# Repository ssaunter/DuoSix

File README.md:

# DuoSix
DuoSix is a 6-key, dual-encoder macropad powered by a Seeed Studio XIAO RP2040 and a PCF8574N IO Expander. 

Right now, the buttons are just bound to media controls, but I intend to update the code in the future to store "libraries" of key presets based on different apps or uses, which can be navigated and selected through the OLED and one of the encoders.

I made this project to learn how to use some new programs, while challenging myself to make something that I'll want to use for a long time. While I have experience in CAD and some of EDA in fusion, I had zero expereience in KiCad or Github before this project, so figuring everything out over about four days felt great.

---
**DuoSix Full Assembly**

---

**KiCad Schematic**

---

**KiCad PCB Routing**

---

**Case and PCB Fitment**

This design utilizes mostly press-fit connection. The PCB is mounted to the bottom case using M3x6 screws, and the diffusing ring is set in place around it, and in contact with the base. The diffusing ring is then slotted into the top case, holding the case together. I also made knobs to press-fit onto the rotary encoders.

---
### Bill of Materials (BOM)

**Included:**
* 1x Seeed Studio XIAO RP2040
* 6x MX-Style switches
* 6x DSA keycaps
* 2x EC11 rotary encoders
* 1x 0.91 inch OLED display
* 6x 1N4148 diodes
* 8x SK6812 MINI-E LEDs
* 4x M3x5mx4mm heatset inserts
* 3D Printed Case Components (Top, Bottom, Diffuser)

**Self Sourced:**
* 1x PCF8574N IO expander
* 1x 4 pin female socket (raises OLED up)
* 4x M3x6mm screws

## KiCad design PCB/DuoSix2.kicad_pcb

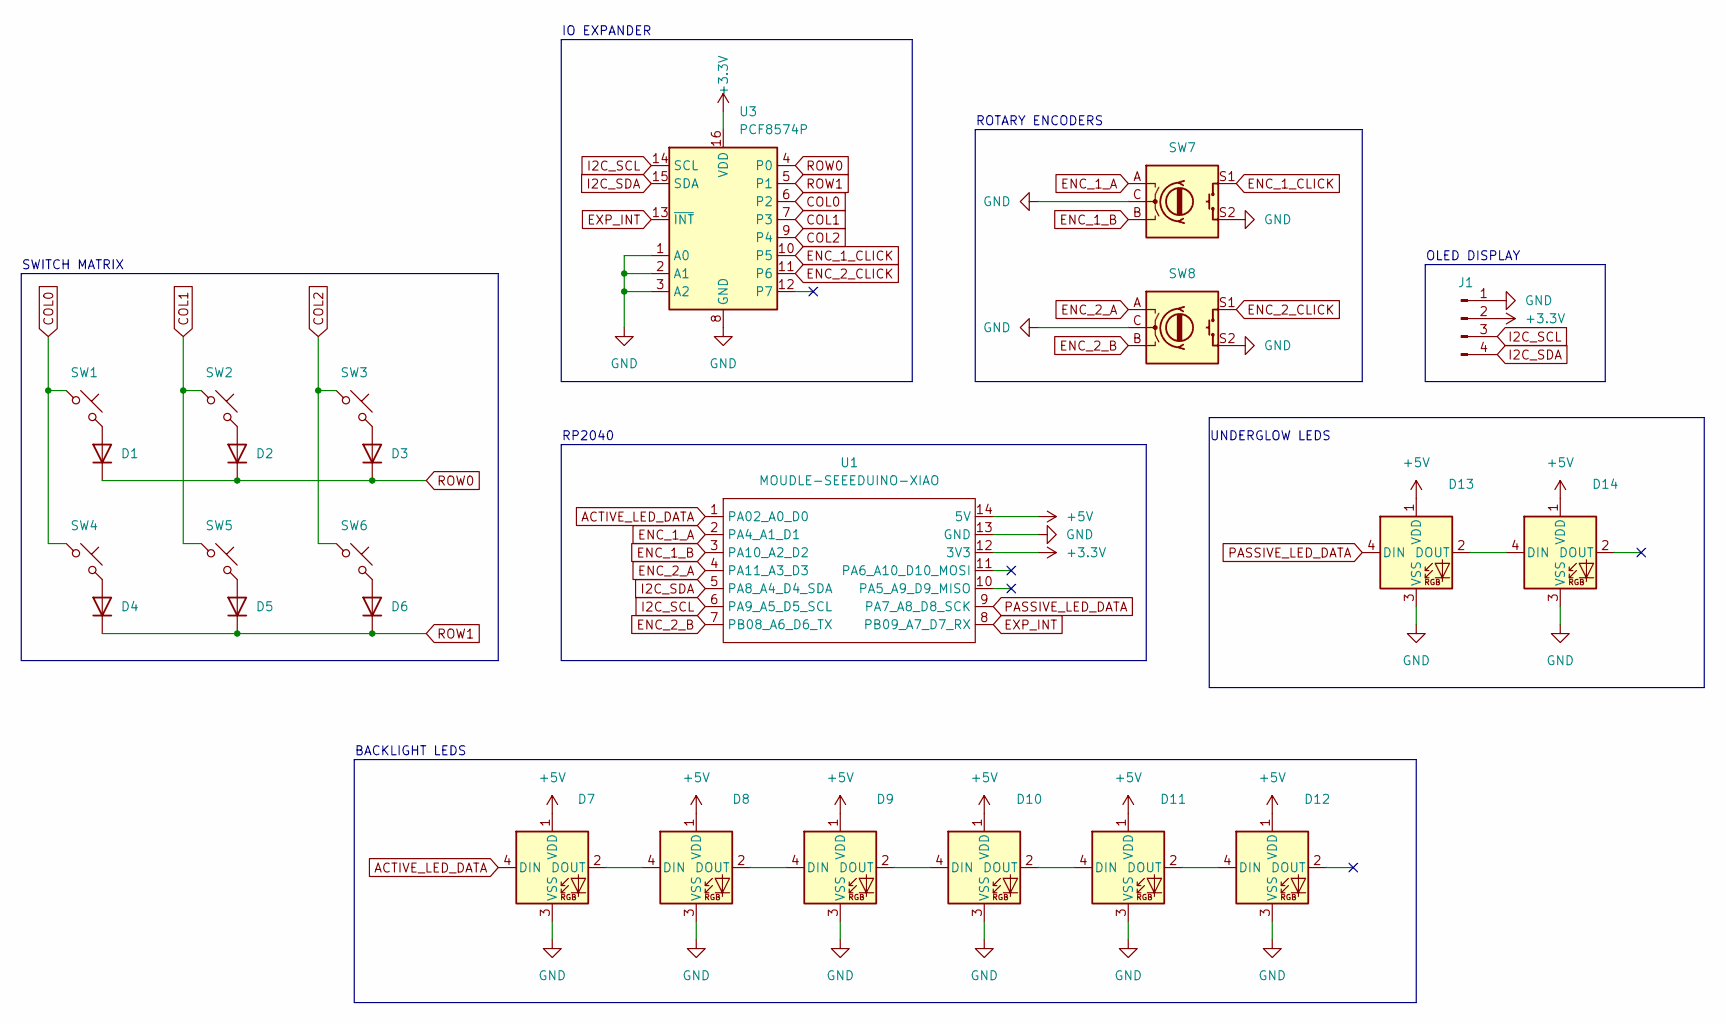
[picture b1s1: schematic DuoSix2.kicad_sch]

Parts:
D1, D2, D3, D4, D5, D6: 1N4148; D_DO-35_SOD27_P7.62mm_Horizontal
D7, D8, D9, D10, D11, D12, D13, D14: SK6812MINI-E; SK6812MINI-E_fixed
J1: OLED_DISPLAY; SSD1306-0.91-OLED-4pin-128x32
SW1, SW2, SW3, SW4, SW5, SW6: SW_Push_45deg; SW_Cherry_MX_1.00u_PCB
SW7, SW8: RotaryEncoder_Switch; RotaryEncoder_Alps_EC11E-Switch_Vertical_H20mm
U1: MOUDLE-SEEEDUINO-XIAO; XIAO-Generic-Hybrid-14P-2.54-21X17.8MM
U3: PCF8574P; DIP-16_W7.62mm

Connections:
+3.3V: J1.2, U1.12 (3V3), U3.16 (VDD)
+5V: D7.1 (VDD), D8.1 (VDD), D9.1 (VDD), D10.1 (VDD), D11.1 (VDD), D12.1 (VDD), D13.1 (VDD), D14.1 (VDD), U1.14 (5V)
ACTIVE_LED_DATA: D7.4 (DIN), U1.1 (PA02_A0_D0)
COL0: SW1.1, SW4.1, U3.6 (P2)
COL1: SW2.1, SW5.1, U3.7 (P3)
COL2: SW3.1, SW6.1, U3.9 (P4)
ENC_1_A: SW7.A, U1.2 (PA4_A1_D1)
ENC_1_B: SW7.B, U1.3 (PA10_A2_D2)
ENC_1_CLICK: SW7.S1, U3.10 (P5)
ENC_2_A: SW8.A, U1.4 (PA11_A3_D3)
ENC_2_B: SW8.B, U1.7 (PB08_A6_D6_TX)
ENC_2_CLICK: SW8.S1, U3.11 (P6)
EXP_INT: U1.8 (PB09_A7_D7_RX), U3.13 (~INT)
GND: D7.3 (VSS), D8.3 (VSS), D9.3 (VSS), D10.3 (VSS), D11.3 (VSS), D12.3 (VSS), D13.3 (VSS), D14.3 (VSS), J1.1, SW7.C, SW7.S2, SW8.C, SW8.S2, U1.13 (GND), U3.1 (A0), U3.2 (A1), U3.3 (A2), U3.8 (GND)
I2C_SCL: J1.3, U1.6 (PA9_A5_D5_SCL), U3.14 (SCL)
I2C_SDA: J1.4, U1.5 (PA8_A4_D4_SDA), U3.15 (SDA)
unnamed: D1.2 (A), SW1.2
unnamed: D2.2 (A), SW2.2
unnamed: D3.2 (A), SW3.2
unnamed: D4.2 (A), SW4.2
unnamed: D5.2 (A), SW5.2
unnamed: D6.2 (A), SW6.2
unnamed: D7.2 (DOUT), D8.4 (DIN)
unnamed: D8.2 (DOUT), D9.4 (DIN)
unnamed: D9.2 (DOUT), D10.4 (DIN)
unnamed: D10.2 (DOUT), D11.4 (DIN)
unnamed: D11.2 (DOUT), D12.4 (DIN)
unnamed: D13.2 (DOUT), D14.4 (DIN)
PASSIVE_LED_DATA: D13.4 (DIN), U1.9 (PA7_A8_D8_SCK)
ROW0: D1.1 (K), D2.1 (K), D3.1 (K), U3.4 (P0)
ROW1: D4.1 (K), D5.1 (K), D6.1 (K), U3.5 (P1)

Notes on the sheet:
IO EXPANDER
UNDERGLOW LEDS
SWITCH MATRIX
BACKLIGHT LEDS
OLED DISPLAY
RP2040
ROTARY ENCODERS

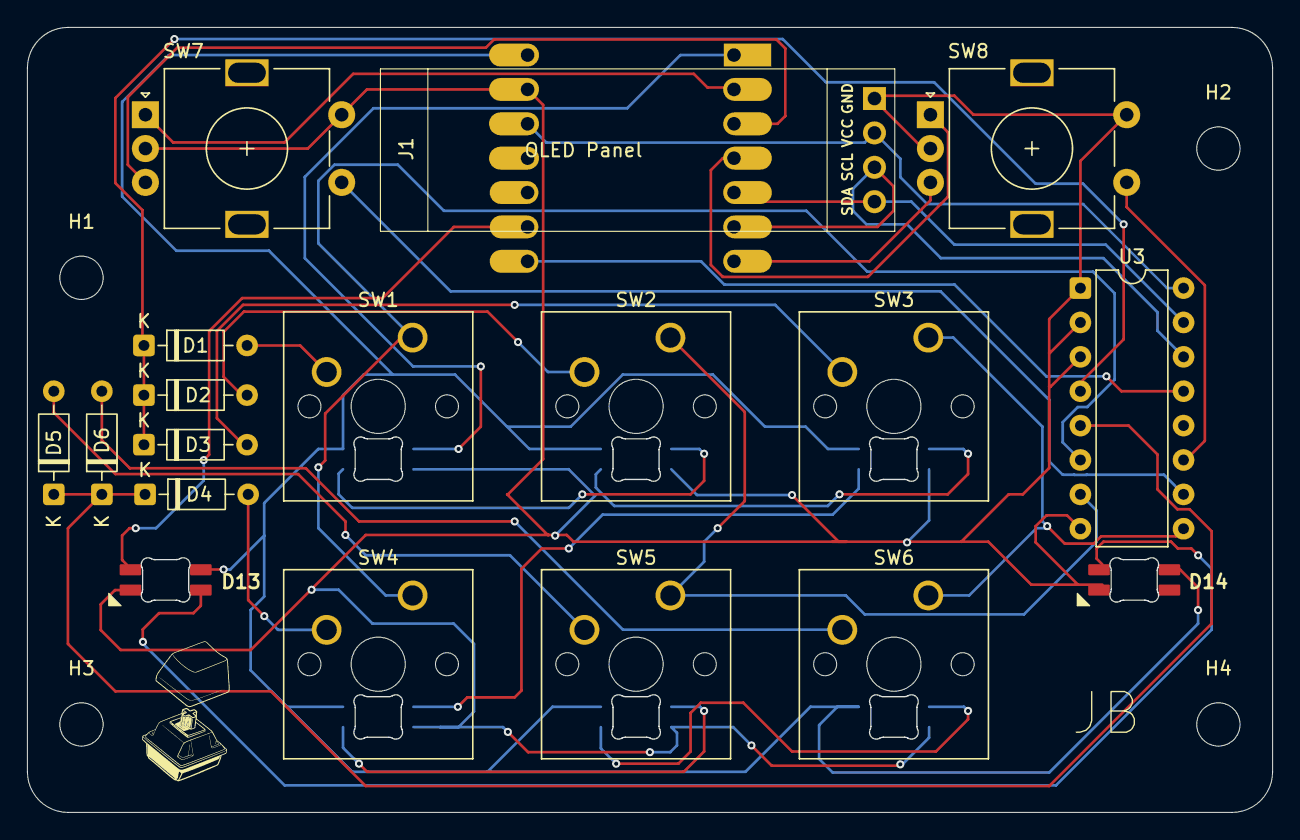
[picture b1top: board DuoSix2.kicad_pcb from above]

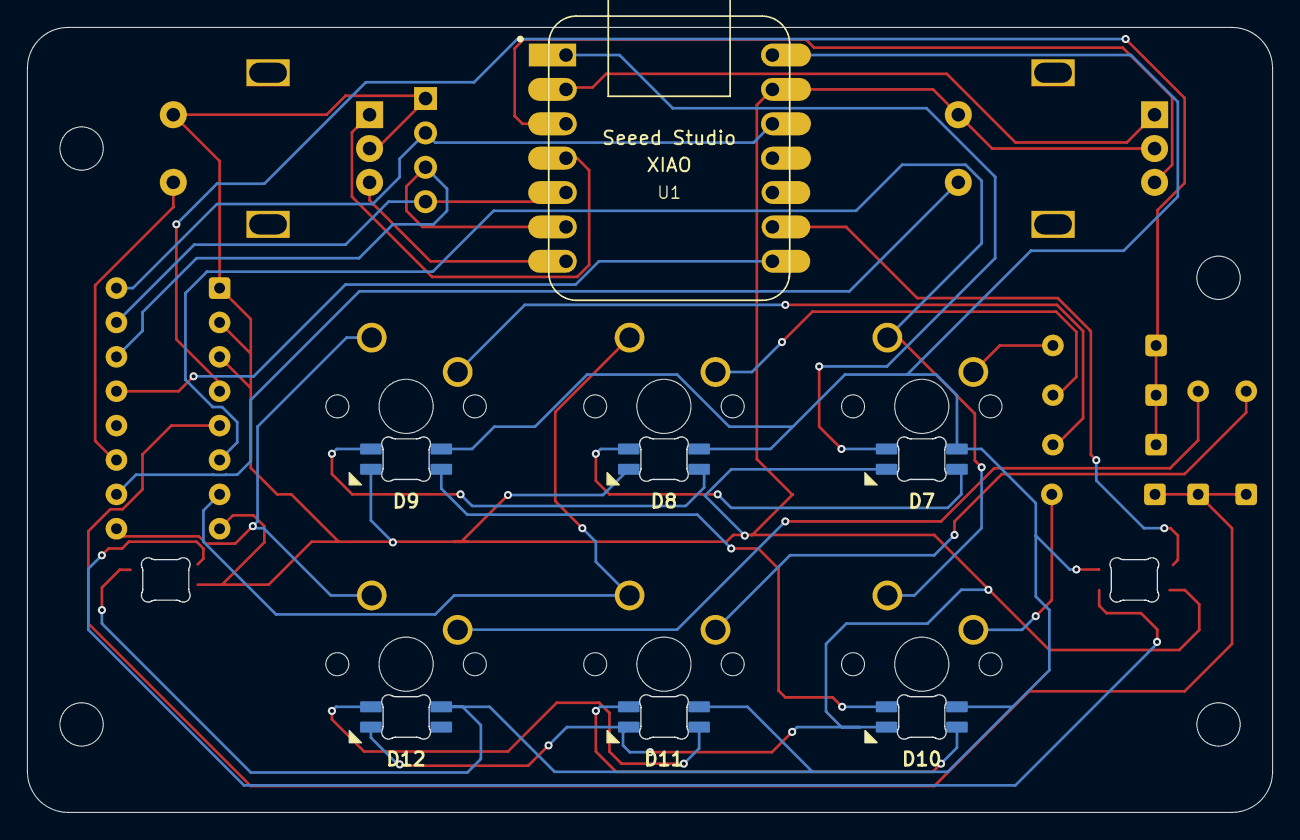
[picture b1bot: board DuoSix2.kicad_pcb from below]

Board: 2 copper layers, 92.0 x 58.0 mm, 29 parts (3 on the bottom side), 31 nets.

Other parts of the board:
H1, H2, H3, H4: MountingHole_3.2mm_M3

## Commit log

2026-03-06 Initial upload of DuoSix files
2026-03-06 Added BOM and F3Z cad file
2026-03-06 Update README.md
    Added more descriptions to follow the submission reqs.
2026-03-08 Altered Design
    Removed decoupling capacitors and IC socket to reduce production cost
2026-03-08 Updated BOM
    Included prices and running total
2026-03-09 Updated PCB
    Forgot some traces after changing model in last version
2026-03-10 Updated Images
    Changed images to reflect newest version of PCB & case
